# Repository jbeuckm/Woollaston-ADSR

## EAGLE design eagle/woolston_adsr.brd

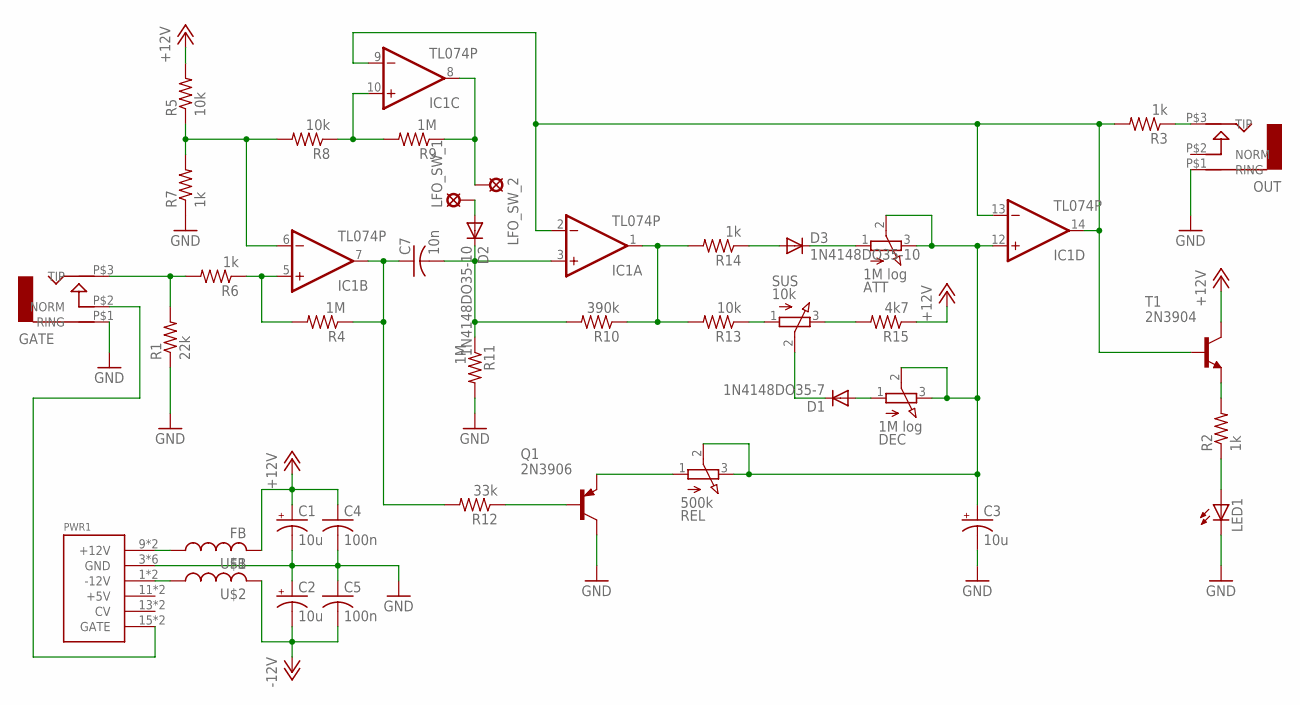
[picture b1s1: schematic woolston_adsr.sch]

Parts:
ATT: 1M log; 3RP/1610N
C1, C2, C3: 10u; B45181A
C4, C5: 100n; C050-024X044
C7: 10n; C050-024X044
D1: 1N4148DO35-7; DO35-7
D2, D3: 1N4148DO35-10; DO35-10
DEC: 1M log; 3RP/1610N
GATE: AUDIO-JACK; ERTHENVAR-JACK-90DEG
IC1: TL074P; DIL14
LED1: LED5MM
LFO_SW_1, LFO_SW_2: LSP11
OUT: AUDIO-JACK; ERTHENVAR-JACK-90DEG
PWR1: POWER; POWER_16
Q1: 2N3906; TO92
R1: 22k; 0207/10
R2, R3, R6, R7, R14: 1k; 0207/10
R4, R9, R11: 1M; 0207/10
R5, R8, R13: 10k; 0207/10
R10: 390k; 0207/10
R12: 33k; 0207/10
R15: 4k7; 0207/10
REL: 500k; 3RP/1610N
SUS: 10k; 3RP/1610N
T1: 2N3904; TO92
U$1, U$2: FB

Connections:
+12V: C1.+, C4.1, R5.2, R15.1, T1.1 (C), U$1.P$2 (2)
-12V: C2.-, C5.2, U$2.P$2 (2)
GND: C1.-, C2.+, C3.-, C4.2, C5.1, GATE.P$1 (RING), LED1.K (C), OUT.P$1 (RING), PWR1.3 (GND), PWR1.4 (GND), PWR1.5 (GND), PWR1.6 (GND), PWR1.7 (GND), PWR1.8 (GND), Q1.1 (C), R1.1, R7.1, R11.2
unnamed: PWR1.9 (+12V), PWR1.10 (+12V), U$1.P$1 (1)
unnamed: PWR1.1 (-12V), PWR1.2 (-12V), U$2.P$1 (1)
unnamed: Q1.3 (E), REL.1 (A)
unnamed: C7.1, IC1.7 (OUT), R4.1, R12.2
unnamed: R2.2, T1.3 (E)
unnamed: IC1.5 (+IN), R4.2, R6.1
unnamed: IC1.6 (-IN), R5.1, R7.2, R8.2
unnamed: LED1.A, R2.1
unnamed: D2.A, LFO_SW_1.MP
unnamed: IC1.10 (+IN), R8.1, R9.2
unnamed: Q1.2 (B), R12.1
unnamed: GATE.P$2 (NORM), PWR1.15 (GATE), PWR1.16 (GATE)
unnamed: IC1.8 (OUT), LFO_SW_2.MP, R9.1
unnamed: GATE.P$3 (TIP), R1.2, R6.2
unnamed: OUT.P$3 (TIP), R3.1
unnamed: R13.1, SUS.1 (A)
unnamed: C7.2, D2.C, IC1.3 (+IN), R10.2, R11.1
unnamed: IC1.2 (-IN), IC1.9 (-IN), IC1.13 (-IN), IC1.14 (OUT), R3.2, T1.2 (B)
unnamed: IC1.1 (OUT), R10.1, R13.2, R14.2
unnamed: D3.A, R14.1
unnamed: R15.2, SUS.3 (E)
unnamed: ATT.1 (A), D3.C
unnamed: D1.A, DEC.1 (A)
unnamed: D1.C, SUS.2 (S)
unnamed: ATT.2 (S), ATT.3 (E), C3.+, DEC.2 (S), DEC.3 (E), IC1.12 (+IN), REL.2 (S), REL.3 (E)
V+: IC1.4 (V+)
V-: IC1.11 (V-)

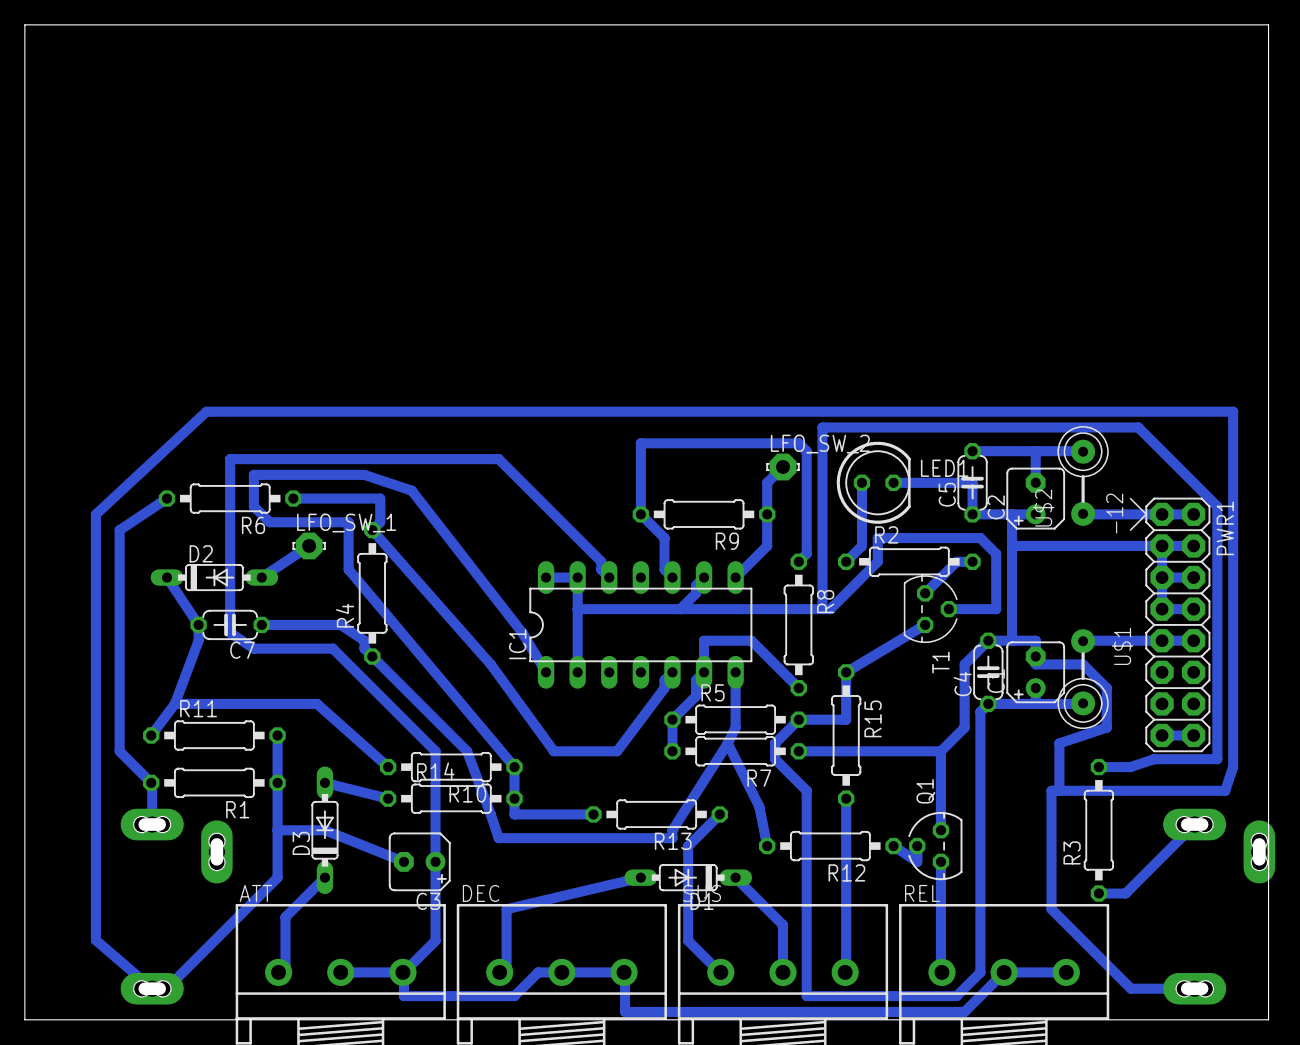
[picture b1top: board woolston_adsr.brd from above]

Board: 2 copper layers, 99.0 x 79.0 mm, 39 parts (0 on the bottom side), 28 nets.

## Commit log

2015-12-31 schematic
2016-01-01 almost layout
2016-01-01 fixed power to 074 and twiggled some
2016-01-05 verified and new panel
